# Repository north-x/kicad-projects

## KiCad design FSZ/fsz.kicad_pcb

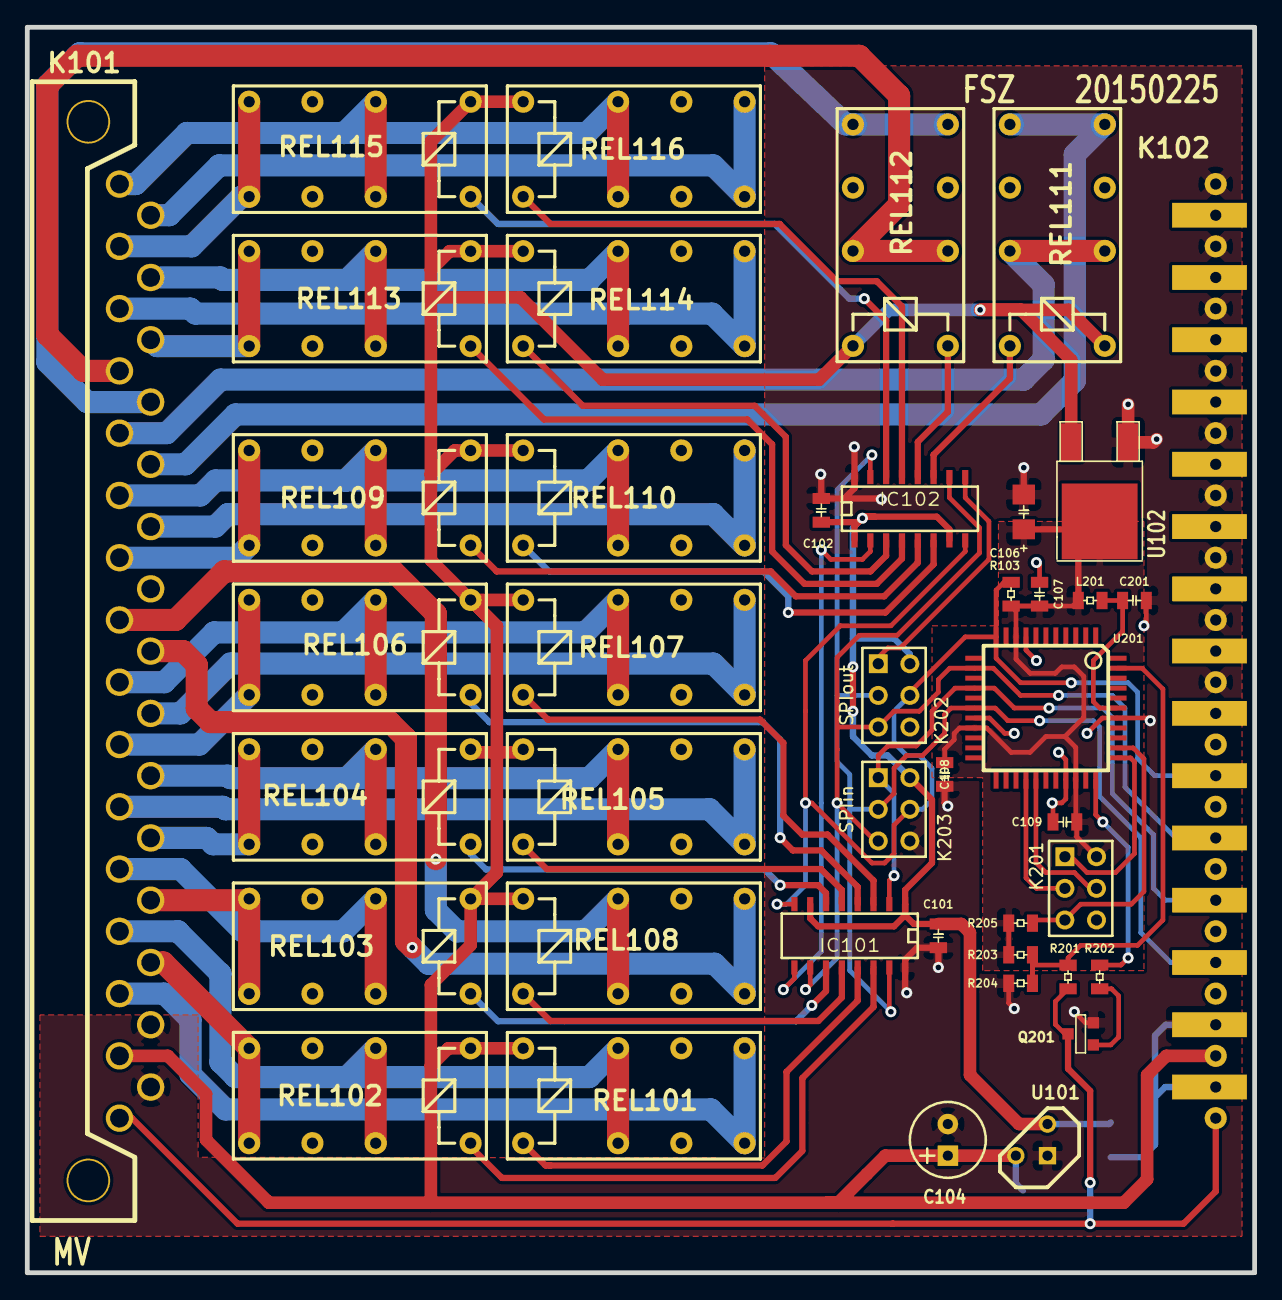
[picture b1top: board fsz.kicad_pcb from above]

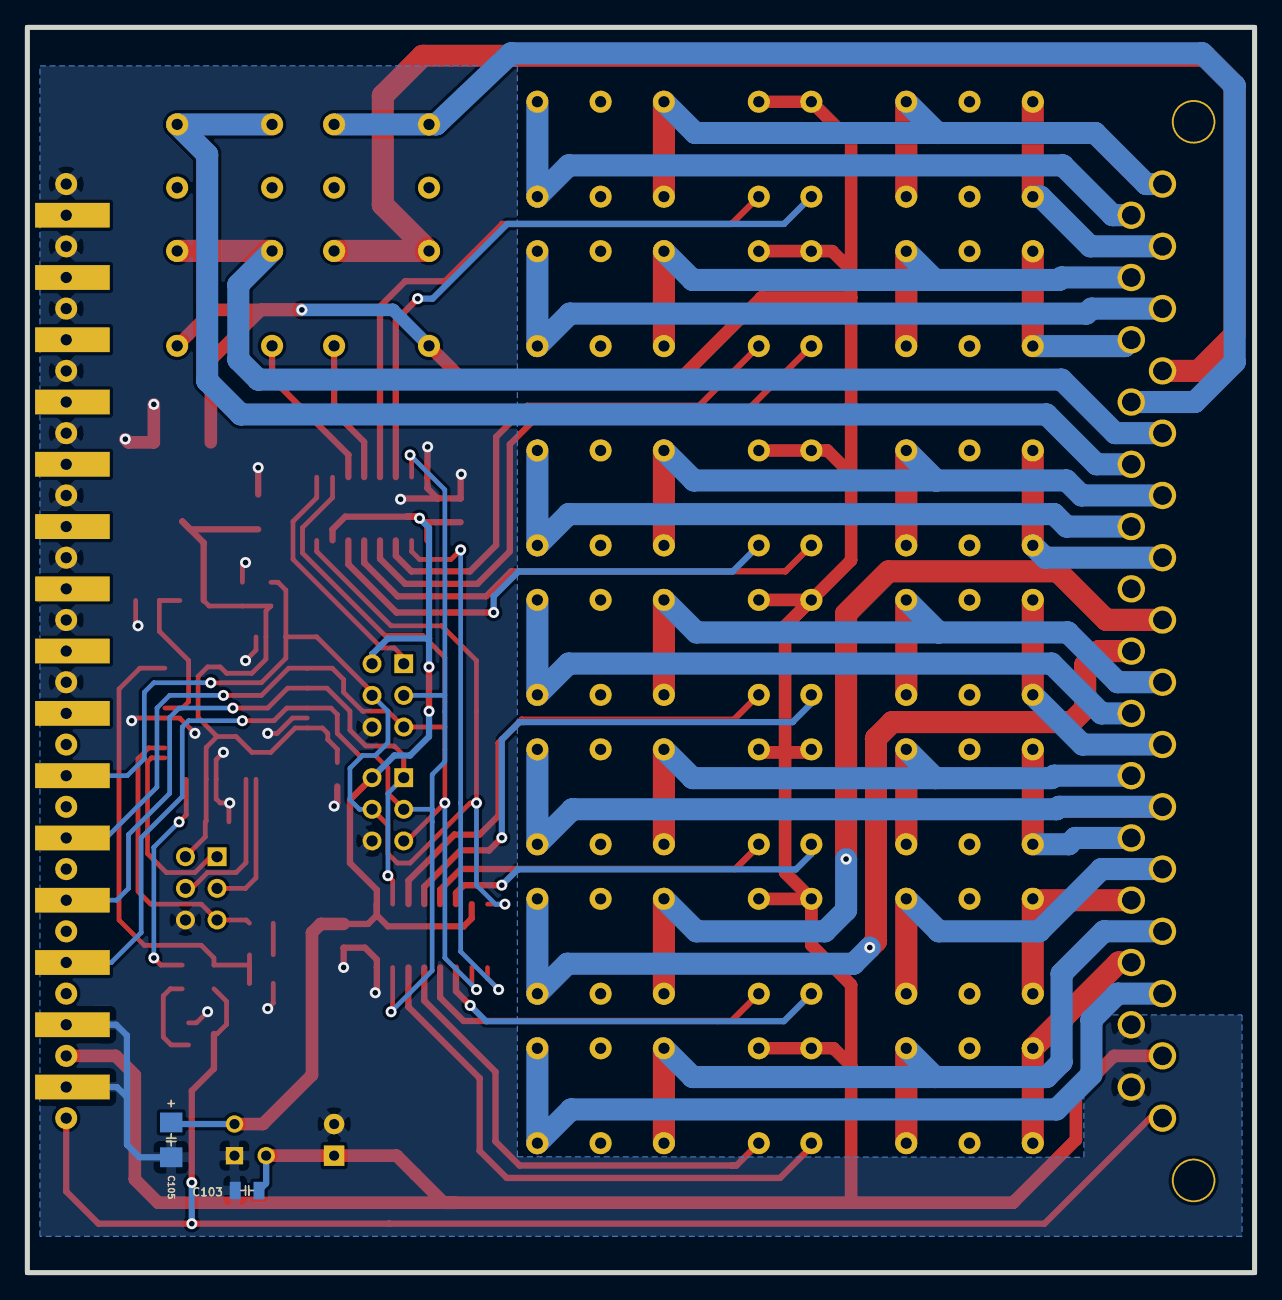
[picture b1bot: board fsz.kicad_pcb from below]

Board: 2 copper layers, 98.6 x 100.0 mm, 44 parts (2 on the bottom side), 77 nets.

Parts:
C101, C102, C103: 100n; C0805
C104: 33u; C1V6
C105: 10u; C1206Pol
C106: 10uF; C1206Pol
C107, C108, C109, C201: 100nF; C0805
IC101, IC102: TPIC6C596D; SO16E
K101: DIN41617; DIN41617-31
K102: DIN41617; DIN41617_Bu
K201: ISP6; header_3x2
K202: SPIout; header_3x2
K203: SPIin; header_3x2
L201: 10uH; R0805
Q201: BC848; SOT23EBC
R103: R; R0805
R201: 68k; R0805
R202: 1k; R0805
R203, R204, R205: 10k; R0805
REL101, REL102, REL103, REL104, REL105, REL106, REL107, REL108, REL109, REL110, REL111, REL112, REL113, REL114, REL115, REL116: MT2 C93402; Relay_MT2
U101: 78L05; LM78LXX
U102: LD1117; DPAK2-Reg
U201: ATXMEGA32A4U; TQFP44

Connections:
+3.3V: C106.1, C107.1, C108.1, C109.1, K201.2, L201.1, R103.1, R203.1, R205.1, U102.VO, U201.9, U201.19, U201.31
+5V: C101.1, C102.1, C105.1, IC101.1, IC101.7, IC102.1, IC102.7, K202.2, K203.2, U101.VO
+12V: C103.1, C104.1, K101.3, K102.3, REL101.2, REL102.1, REL103.1, REL104.1, REL105.2, REL106.1, REL107.2, REL108.2, REL109.1, REL110.2, REL111.1, REL112.2, REL113.1, REL114.2, REL115.1, REL116.2, U101.VI, U102.VI
/A1: K101.5, REL101.5, REL101.8
/A2: K101.8, REL103.5, REL103.8
/A3: K101.10, REL104.5, REL104.8
/A4: K101.13, REL106.5, REL106.8
/A5: K101.16, REL108.5, REL108.8
/A6: K101.19, REL109.5, REL109.8
/A7: K101.22, REL111.5, REL111.8
/A8: K101.24, REL112.5, REL112.8
/A9: K101.26, REL113.5, REL113.8
/A10: K101.29, REL115.5, REL115.8
/B1: K101.6, REL102.5, REL102.8
/B3: K101.11, REL105.5, REL105.8
/B4: K101.14, REL107.5, REL107.8
/B6: K101.20, REL110.5, REL110.8
/B9: K101.27, REL114.5, REL114.8
/B10: K101.30, REL116.5, REL116.8
/C1: K101.7, REL101.3, REL101.6, REL102.3, REL102.6
/C2: K101.9, REL103.3, REL103.6
/C3: K101.12, REL104.3, REL104.6, REL105.3, REL105.6
/C4: K101.15, REL106.3, REL106.6, REL107.3, REL107.6
/C5: K101.17, REL108.3, REL108.6
/C6: K101.21, REL109.3, REL109.6, REL110.3, REL110.6
/C7: K101.23, REL111.3, REL111.6
/C8: K101.25, REL112.3, REL112.6
/C9: K101.28, REL113.3, REL113.6, REL114.3, REL114.6
/C10: K101.31, REL115.3, REL115.6, REL116.3, REL116.6
/LN: K101.1, K102.1, Q201.3, R201.1
/Rel1: IC101.3, REL107.1
/Rel2: IC101.4, REL106.2
/Rel3: IC101.5, REL105.1
/Rel4: IC101.6, REL104.2
/Rel5: IC101.11, REL103.2
/Rel6: IC101.12, REL108.1
/Rel7: IC101.13, REL101.1
/Rel8: IC101.14, REL102.2
/Rel11: IC102.3, REL114.1
/Rel12: IC102.4, REL113.2
/Rel13: IC102.5, REL109.2
/Rel14: IC102.6, REL110.1
/Rel15: IC102.11, REL111.2
/Rel16: IC102.12, REL112.1
/Rel17: IC102.13, REL116.1
/Rel18: IC102.14, REL115.2
CommRX: R201.2, R203.2, R204.1, U201.43
CommTX: R202.2, U201.33
D+/Tx: K201.4, U201.27
D-/Rx: K201.3, U201.26
GND: C101.2, C102.2, C103.2, C104.2, C105.2, C106.2, C107.2, C108.2, C109.2, C201.2, IC101.16, IC102.16, K101.2, K101.4, K102.2, K102.4, K102.15, K102.17, K102.19, K102.21, K102.23, K102.25, K102.27, K102.29, K102.31, K201.6, K202.6, K203.6, Q201.1, R204.2, U101.GND, U102.GND, U201.8, U201.18, U201.30, U201.38
unnamed: C201.1, L201.2, U201.39
unnamed: IC101.9, IC102.2
unnamed: K201.1, U201.34
unnamed: K201.5, R205.2, U201.35
unnamed: Q201.2, R202.1
unnamed: REL101.4, REL101.7
unnamed: REL102.4, REL102.7
unnamed: REL103.4, REL103.7
unnamed: REL104.4, REL104.7
unnamed: REL105.4, REL105.7
unnamed: REL106.4, REL106.7
unnamed: REL107.4, REL107.7
unnamed: REL108.4, REL108.7
unnamed: REL109.4, REL109.7
unnamed: REL110.4, REL110.7
unnamed: REL111.4, REL111.7
unnamed: REL112.4, REL112.7
unnamed: REL113.4, REL113.7
unnamed: REL114.4, REL114.7
unnamed: REL115.4, REL115.7
unnamed: REL116.4, REL116.7
SPI_MISO: IC102.9, K202.1
SPI_MOSI: IC101.2, K102.8, K203.1, U201.15
SPI_OE: IC101.8, IC102.8, K102.12, K202.4, K203.4, R103.2, U201.11
SPI_RCK: IC101.10, IC102.10, K102.10, K202.5, K203.5, U201.13
SPI_SCK: IC101.15, IC102.15, K102.6, K202.3, K203.3, U201.17

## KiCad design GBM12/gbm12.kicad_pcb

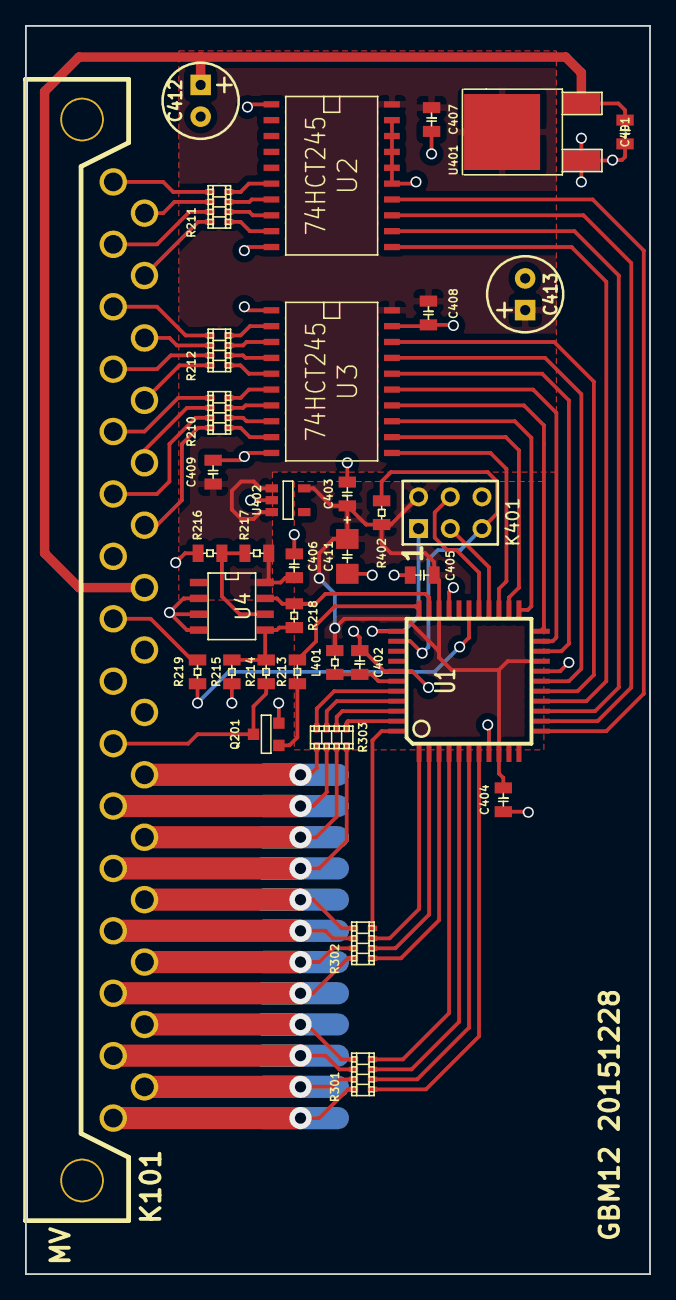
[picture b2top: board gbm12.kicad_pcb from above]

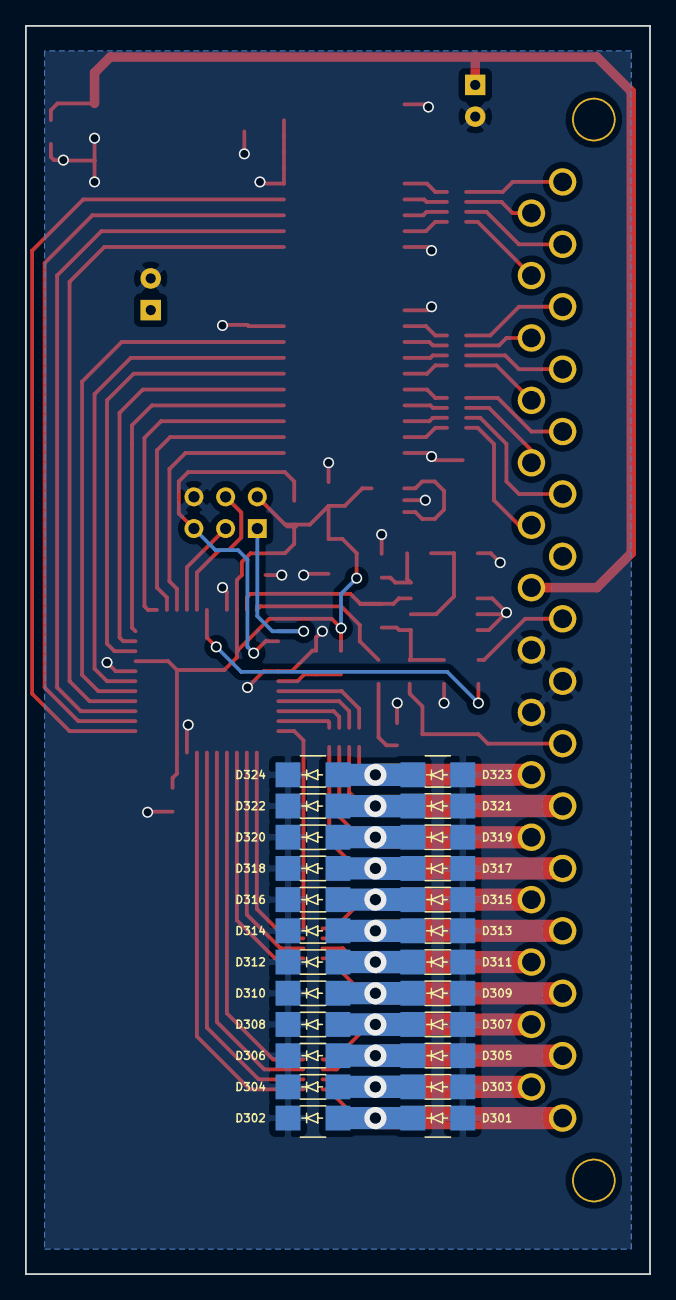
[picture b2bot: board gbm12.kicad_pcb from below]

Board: 2 copper layers, 50.0 x 100.0 mm, 60 parts (24 on the bottom side), 77 nets.

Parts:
C401, C402, C403, C404, C405, C406, C407, C408, C409: 100nF; C0805
C411: 10uF; C1206Pol
C412, C413: 33uF; C1V6
D301, D302, D303, D304, D305, D306, D307, D308, D309, D310, D311, D312, D313, D314, D315, D316, D317, D318, D319, D320, D321, D322, D323, D324: DIODE; DSMA
K101: DIN41617; DIN41617-31
K401: ISP6; header_3x2
L401: 10uH; R0805
Q201: BC848; SOT23EBC
R210, R211, R212, R301, R302, R303: 1k; R1206x4
R213: 1k; R0805
R214: 47k; R0805
R215: 150k; R0805
R216: 39k; R0805
R217: 27k; R0805
R218: 240k; R0805
R219: 100k; R0805
R402: 10k; R0805
U1: ATxmegaxA4U; TQFP44
U2, U3: 74HCT245; SO20L
U4: LM393; SO8E
U401: LD1117; DPAK2-Reg
U402: LP2985; SOT23-5

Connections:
+3.3V: C403.1, C404.1, C405.1, C411.1, K401.2, L401.1, R402.1, U1.9, U1.19, U1.31, U402.5
+5V: C406.1, C407.1, C408.1, C409.1, C413.1, R217.1, U2.20, U3.20, U4.8, U401.VO, U402.1, U402.3
/BM1: K101.30, R211.6
/BM2: K101.29, R211.4
/BM3: K101.26, R212.6
/BM4: K101.27, R212.8
/BM5: K101.20, R210.2
/BM6: K101.21, R210.4
/BM7: K101.24, R212.2
/BM8: K101.25, R212.4
/BM9: K101.28, R211.2
/BM10: K101.31, R211.8
/BM11: K101.23, R210.8
/BM12: K101.22, R210.6
/Comm: K101.13, Q201.3, R214.1
/G1: D301.2, D302.1, K101.1, R301.7
/G2: D303.2, D304.1, K101.2, R301.5
/G3: D305.2, D306.1, K101.3, R301.3
/G4: D307.2, D308.1, K101.4, R301.1
/G5: D309.2, D310.1, K101.5, R302.7
/G6: D311.2, D312.1, K101.6, R302.5
/G7: D313.2, D314.1, K101.7, R302.3
/G8: D315.2, D316.1, K101.8, R302.1
/G9: D317.2, D318.1, K101.9, R303.7
/G10: D319.2, D320.1, K101.10, R303.5
/G11: D321.2, D322.1, K101.11, R303.3
/G12: D323.2, D324.1, K101.12, R303.1
/Interface/TrigIn: K101.17, R219.2
/S1: R301.8, U1.7
/S2: R301.6, U1.6
/S3: R301.4, U1.5
/S4: R301.2, U1.4
/S5: R302.8, U1.3
/S6: R302.6, U1.2
/S7: R302.4, U1.1
/S8: R302.2, U1.44
/S9: R303.8, U1.43
/S10: R303.6, U1.42
/S11: R303.4, U1.41
/S12: R303.2, U1.40
CommRX: R218.1, U1.32, U4.7
CommTX: R213.2, U1.33
D+/Tx: K401.4, U1.27
D-/Rx: K401.3, U1.26
GND: C401.2, C402.2, C403.2, C404.2, C405.2, C406.2, C407.2, C408.2, C409.2, C411.2, C412.2, C413.2, D301.1, D302.2, D303.1, D304.2, D305.1, D306.2, D307.1, D308.2, D309.1, D310.2, D311.1, D312.2, D313.1, D314.2, D315.1, D316.2, D317.1, D318.2, D319.1, D320.2, D321.1, D322.2, D323.1, D324.2, K101.14, K101.15, K101.16, K401.6, Q201.1, R215.2, R216.2, U1.8, U1.18, U1.30, U1.38, U2.1, U2.10, U2.15, U2.16, U2.17, U2.18, U2.19, U3.1, U3.10, U3.19, U4.2, U4.3, U4.4, U401.GND, U402.2
unnamed: C402.1, L401.2, U1.39
unnamed: K401.1, U1.34
unnamed: K401.5, R402.2, U1.35
unnamed: Q201.2, R213.1
unnamed: R210.1, U3.9
unnamed: R210.3, U3.8
unnamed: R210.5, U3.7
unnamed: R210.7, U3.6
unnamed: R211.1, U2.9
unnamed: R211.3, U2.8
unnamed: R211.5, U2.7
unnamed: R211.7, U2.6
unnamed: R212.1, U3.5
unnamed: R212.3, U3.4
unnamed: R212.5, U3.3
unnamed: R212.7, U3.2
unnamed: R214.2, R215.1, R218.2, U4.5
unnamed: R216.1, R217.2, U4.6
unnamed: R219.1, U1.28
unnamed: U1.12, U2.14
unnamed: U1.13, U2.13
unnamed: U1.14, U2.12
unnamed: U1.15, U2.11
unnamed: U1.16, U3.18
unnamed: U1.17, U3.17
unnamed: U1.20, U3.16
unnamed: U1.21, U3.15
unnamed: U1.22, U3.14
unnamed: U1.23, U3.13
unnamed: U1.24, U3.12
unnamed: U1.25, U3.11
Vin: C401.1, C412.1, K101.18, U401.VI
